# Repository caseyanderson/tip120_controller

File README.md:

# tip120_controller
Casey Anderson, 2018

## Overview

This repository provides `Printed Circuit Board` (`PCB`) files, as well as software examples, for an Arduino-based `TIP120` actuator controlled via `Potentiometer` (or any `Voltage Divider`). As described (in more detail) [here](http://bildr.org/2011/03/high-power-control-with-arduino-and-tip120/), the `TIP120` is capable of actuating a variety of devices including brushless DC motors, vibration motors, solenoids, and lightbulbs.

## PCB

This double-sided `Pin Through Hole` (`PTH`) PCB was created in EAGLE.

`VCC` is supplied to the `Arduino Mini` via `RAW` (12V maximum). `VCC` is also passed to the `T` pin of the `CONN JACK STEREO 3.5MM`. Connection to motors/solenoids/whatever is accomplished via 3.5mm audio cable. Rate of actuation is set via `Potentiometer` and passed to `Arduino Mini` via `A0`.

### BOM

Note: items without a `Manufacturer Part Number` are generic.

* 1x Arduino Pro Mini (3.3V, 8MHz)
* 1x SWITCH SLIDE SPDT 200MA 30V, `EG1218`
* 1x CONN PWR JACK 2X5.5MM SOLDER, `PJ-102A`
* 1x CONN JACK STEREO 3.5MM, `SJ1-3523N`
* 1x POT 10kR 1/20W CARBON LOG, `PTV09A-4020F-A103`
* 1x TIP120
* 1x 1N4004 Diode
* 1x 220R
* 1x 2.2kR
* 1x 5mm LED
* 1x Motor/Solenoid/Light

### Photo

## SOFTWARE

Currently only the absolute simplest example of PWM. More to follow.

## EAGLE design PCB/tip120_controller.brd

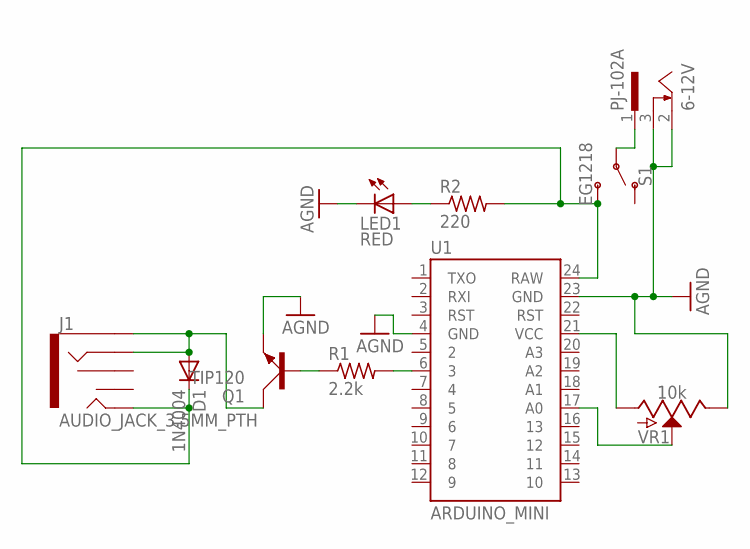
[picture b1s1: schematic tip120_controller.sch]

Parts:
D1: 1N4004; DO41-10
J1: AUDIO_JACK_3.5MM_PTH; AUDIO-JACK
LED1: RED; LED5MM
PJ-102A: 6-12V; SCD-014-A
Q1: TIP120; TO220AV
R1: 2.2k; 0204V
R2: 220; 0204V
S1: EG1218; SWITCH_SPDT_PTH_11.6X4.0MM_LOCK
U1: ARDUINO_MINI
VR1: 10k; POT-PTH-ALPS

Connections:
AGND: LED1.K (C), PJ-102A.2, PJ-102A.3, Q1.E, U1.4 (GND), U1.23 (GND), VR1.P$1 (E)
unnamed: R1.2, U1.6 (3)
unnamed: Q1.B, R1.1
unnamed: LED1.A, R2.1
unnamed: D1.A, J1.RING, J1.SLEEVE, Q1.C
unnamed: U1.21 (VCC), VR1.P$3 (A)
unnamed: U1.17 (A0), VR1.P$2 (S)
unnamed: PJ-102A.1, S1.2
unnamed: D1.C, J1.TIP, R2.2, S1.3 (S), U1.24 (RAW)

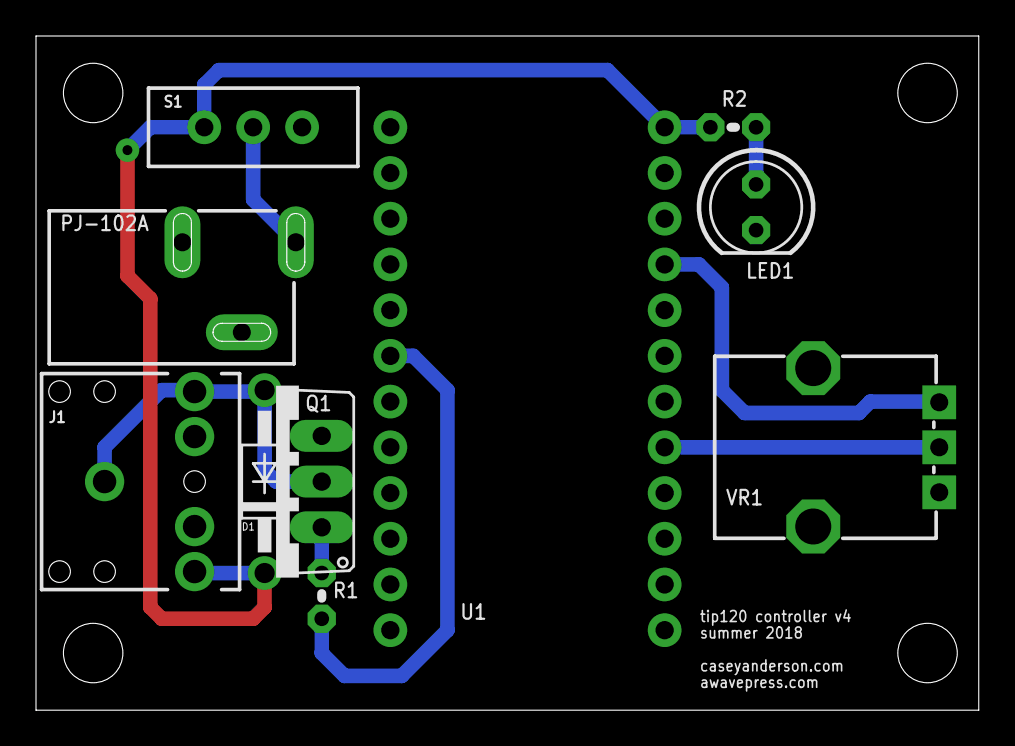
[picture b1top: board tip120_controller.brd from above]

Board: 2 copper layers, 52.4 x 37.5 mm, 14 parts (0 on the bottom side), 9 nets.

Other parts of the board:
U$6, U$7, U$8, U$9: STAND-OFF

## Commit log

2018-03-22 the eagle files
2018-03-22 simple pwm example
2018-03-23 here is a photo + go away ds store
2018-03-23 blah
2018-03-23 edits
2018-03-23 some more notes
2018-03-23 no need to list manufacturer here
2018-03-23 copy edit
2018-03-23 create license
2018-03-23 laksjdf
2018-03-23 uncapitalize wtf
2018-03-23 edit
2018-03-23 copyedit
2018-03-24 solenoid with led
2018-03-26 this works now
2018-03-26 laksdjflkasd
2018-05-03 added ground plane, moved led
2018-05-03 adjust
2018-05-04 moved via so its not under dc jack, layout is done
2018-05-04 silkscreen update
2018-05-04 replaced transistor symbol/footprint, futzing with silkscreen
2018-05-04 sanity check
2018-05-05 no labels for standoffs
2018-05-15 swap footprints, update version number
2018-05-15 reposition switch
2018-05-15 laskjdf
2019-09-08 updated photo with osh park pcb

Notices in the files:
parts and their libraries:
SparkFun-Boards: Licensing: Creative Commons ShareAlike 4.0 International - https://creativecommons.org/licenses/by-sa/4.0
